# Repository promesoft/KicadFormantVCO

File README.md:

# KicadFormantVCO
Started as a Clone of http://sebholzapfel.com/modular-synth-vco-design-build/

# Rev C1 - New PCB

## Status - Rev C1 Produced - received - tested
### Errata
 - RV7 reversed (FM)

### Issues and Notes
 - Consider 10 pin Doepfer (will make routing easier)
 - Place SMD on backside to make better room for components and traces
 - Consider TL074/MC33079
 - 1N4148 footprint - reconsider
 - trimmers on back
 - add resistor to coarse freq trim
 - add swich on PCB for LFO
 - Replace jack connectors 
 - Silk screen is off..
### Alternative components
 - Next should not rely on the LM3046 BJT as its not easy to come by.
 - Next should not rely on the REF102/AD587 as its more expensive than most and not certain if its needed.
 - Consider NAND alternative in oscilator core (74LS00 used for test without problems)
 - consider 1nF cap for VCO core (now 470p)
 - Q4 and Q5 was 2N2222 for test
 - Q1,2,3 was S9013 for the test
 - Op amp was LM833 for the test
 - Mix of 1uF and 4u7 decoupling caps for the test
 - R12 = 390k for the test
 - RV8 = 500R for the test
 - RV7=RV9 = 50k for the test
 - R9 = 240R for the test
 - R18 = 18k for the test
 - R24 = 5k6 for the test
 - R28 = 330R for the test
 
## Physical Construction

## Features

# Rev B
## Old README.md For original PCB
# SMD Formant VCO Prototype
KiCAD files for eurorack-compatible formant-based VCO design. Mostly created just to learn KiCAD.

Video on construction/operation is here: https://www.youtube.com/watch?v=rq4ovZ2om6k

## ERRATA [V1A] (To be fixed in future revision)
- The TL071 op-amp in the CAD files is arbitrary, I actually used an LM358. Just use whatever 8-pin SOIC dual op-amp you like.
- Diodes (D1..) are incorrect footprint. Change this to suit.
- 10V reference chip, VCC is not connected to +V properly. This must be bridged.
- +/-15V designator actually should be +/-12V to match eurorack. Doesn't make any electrical difference, but it's what the schematic says.
- Be careful with tantalum capacitor orientation, check with schematic. Silkscreen 'line' is negative, not positive.

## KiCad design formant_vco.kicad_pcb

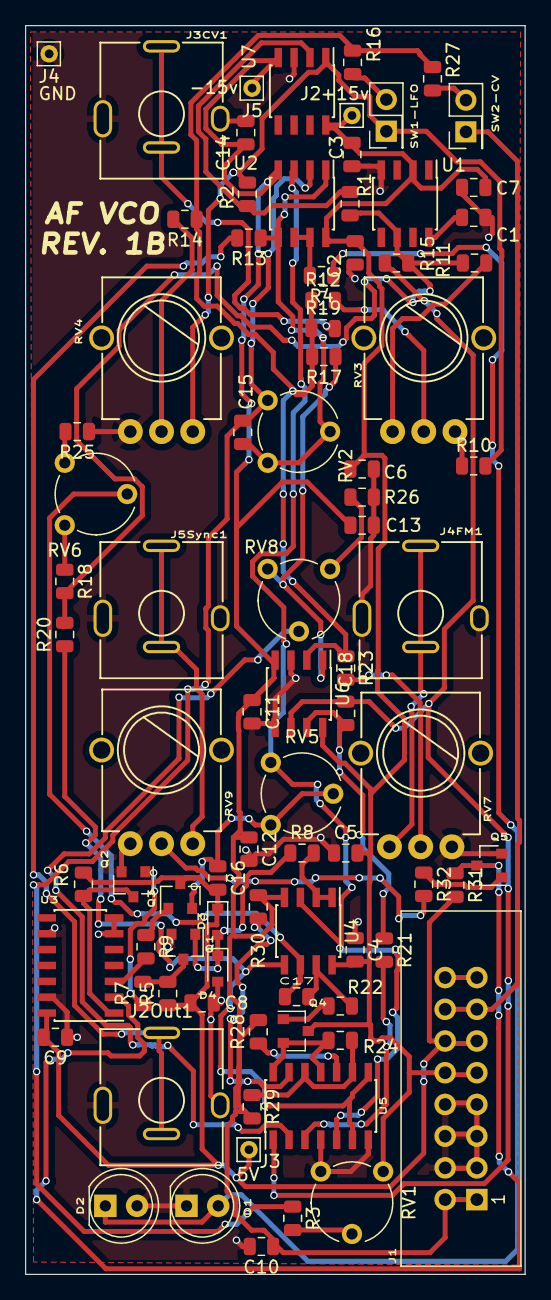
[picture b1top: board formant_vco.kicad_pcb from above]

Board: 2 copper layers, 40.0 x 100.0 mm, 86 parts (0 on the bottom side), 55 nets.

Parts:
C1, C2, C3, C4, C5, C6, C7, C8, C9, C10, C11, C12, C13, C14: 100n; C_0805_2012Metric
C15: 12p; C_0805_2012Metric
C16: 470p; C_0805_2012Metric
C17: 10n; C_0805_2012Metric
C18: 100p; C_0805_2012Metric
D1, D2: LED; LED_D5.0mm
D3, D4: 1N4148; D_0805
J1: CONN_02X08; IDC_Header_Straight_16pins
J2, J3, J4, J5: TEST_1P; Pin_D0.7mm_L6.5mm_W1.8mm_FlatFork
J2Out1: JACK_2P_Out; pj301bm
J3CV1: JACK_2P_CV; pj301bm
J4FM1: JACK_2P_FM; pj301bm
J5Sync1: JACK_2P_Sync; pj301bm
Q1, Q2, Q3, Q4, Q5: BC850; SOT-23
R1, R2, R5, R6, R20: 10K; R_0805_2012Metric
R3, R22: 100R; R_0805_2012Metric
R4, R7, R8, R31, R32: 1K; R_0805_2012Metric
R9: 220R; R_0805_2012Metric
R10, R11, R14, R16, R19, R23, R27: 100K; R_0805_2012Metric
R12: 430K; R_0805_2012Metric
R13: 240R; R_0805_2012Metric
R15: 1M; R_0805_2012Metric
R17: 2K4; R_0805_2012Metric
R18: 20K; R_0805_2012Metric
R21: 56K; R_0805_2012Metric
R24: 6K2; R_0805_2012Metric
R25: 1K2; R_0805_2012Metric
R26: 750R; R_0805_2012Metric
R28: 360R; R_0805_2012Metric
R29: 3K3; R_0805_2012Metric
R30: 330R; R_0805_2012Metric
RV1, RV2, RV6: 10K; Potentiometer_Piher_PT-6-V_Vertical
RV3: 10K LIN Fine; alpha_d_pot_vert
RV4: 100K LIN Coarse; alpha_d_pot_vert
RV5: 5K; Potentiometer_Piher_PT-6-V_Vertical
RV7, RV9: 100K LIN; alpha_d_pot_vert
RV8: 200R; Potentiometer_Piher_PT-6-V_Vertical
SW1-LFO, SW2-CV: SWITCH_SPST; Pin_Header_Straight_2x01_Pitch2.54mm
U1: REF102/AD587; SOIC-8_3.9x4.9mm_P1.27mm
U2, U4, U6, U7: TL072; SOIC-8_3.9x4.9mm_P1.27mm
U3: CD4093; SOIC-14_3.9x8.7mm_Pitch1.27mm
U5: LM3046; SOIC-14_3.9x8.7mm_Pitch1.27mm

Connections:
+5V: C8.2, C9.2, C16.2, D3.1, J1.11, J1.12, J3.1, Q3.3, R5.1, R6.1, R31.2, U3.14
+10V_REF: R1.2, R11.1, R15.2, R18.2, R20.2, U1.6
+15V: C2.2, C3.2, C4.2, C5.2, C6.2, C7.2, J1.9, J1.10, J2.1, Q4.3, RV1.3, U1.2, U2.8, U4.8, U6.8, U7.8
-10V_REF: R2.1, R10.2, RV4.3, SW1-LFO.1, U7.1
-15V: C10.1, C11.1, C12.1, C13.1, C14.1, J1.1, J1.2, J5.1, R28.2, R29.2, R30.2, U2.4, U4.4, U6.4, U7.4
CV_BUS: J1.13, J1.14, SW2-CV.1
GATE_BUS: J1.15, J1.16
GND: C1.2, C2.1, C3.1, C4.1, C5.1, C6.1, C7.1, C8.1, C9.1, C10.2, C11.2, C12.2, C13.2, C14.2, D1.1, D2.2, D4.2, J1.3, J1.4, J1.5, J1.6, J1.7, J1.8, J2Out1.3, J3CV1.3, J4.1, J4FM1.3, J5Sync1.3, Q1.2, Q2.2, Q5.2, R25.1, R26.1, RV1.1, RV4.1, RV7.3, RV9.1, U1.4, U3.6, U3.7, U3.9, U3.13, U5.4, U5.7, U6.3, U6.5, U7.3
unnamed: C1.1, U1.8
unnamed: C15.1, R3.1, RV2.3, U2.2
unnamed: C15.2, R13.1, RV2.1, RV2.2, U2.1, U2.5
unnamed: C16.1, Q3.2, RV5.1, RV5.2
unnamed: C17.1, RV6.2, U4.6
unnamed: C17.2, R22.1, U4.7
unnamed: C18.1, R21.1, U6.7
unnamed: C18.2, R15.1, U5.1, U6.6
unnamed: D1.2, D2.1, R4.1
unnamed: D3.2, D4.1, Q1.1, R8.1
unnamed: J2Out1.1, J2Out1.2, R13.2
unnamed: J3CV1.1, J3CV1.2, R19.2
unnamed: J4FM1.1, J4FM1.2, RV7.1
unnamed: J5Sync1.1, J5Sync1.2, RV9.3
unnamed: Q1.3, R5.2, R7.2
unnamed: Q2.1, R7.1
unnamed: Q2.3, R6.2, U3.1
unnamed: Q3.1, R9.1
unnamed: Q4.1, R22.2
unnamed: Q4.2, R24.1, U5.11, U5.14
unnamed: Q5.1, R32.1
unnamed: R1.1, R2.2, U7.2
unnamed: R3.2, RV1.2
unnamed: R4.2, U2.6, U2.7
unnamed: R8.2, U4.1, U4.2
unnamed: R9.2, U3.3
unnamed: R10.1, RV3.3
unnamed: R11.2, RV3.1
unnamed: R12.1, R14.1, R16.1, R17.2, R19.1, R23.1, R27.1, U6.2
unnamed: R12.2, RV3.2
unnamed: R14.2, RV4.2
unnamed: R16.2, SW1-LFO.2
unnamed: R17.1, RV8.1, U6.1
unnamed: R18.1, RV6.1
unnamed: R20.1, U4.5, U5.6, U5.8
unnamed: R21.2, U5.3
unnamed: R23.2, RV7.2
unnamed: R24.2, R29.1, U5.9, U5.12
unnamed: R25.2, RV6.3
unnamed: R26.2, RV8.3
unnamed: R27.2, SW2-CV.2
unnamed: R28.1, U5.10
unnamed: R30.1, U5.13
unnamed: R32.2, RV9.2
unnamed: RV5.3, U2.3, U4.3, U5.5
unnamed: RV8.2, U5.2
SYNC_IN: Q5.3, R31.1, U3.2

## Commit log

2019-01-10 Init
    Moved files to this project
